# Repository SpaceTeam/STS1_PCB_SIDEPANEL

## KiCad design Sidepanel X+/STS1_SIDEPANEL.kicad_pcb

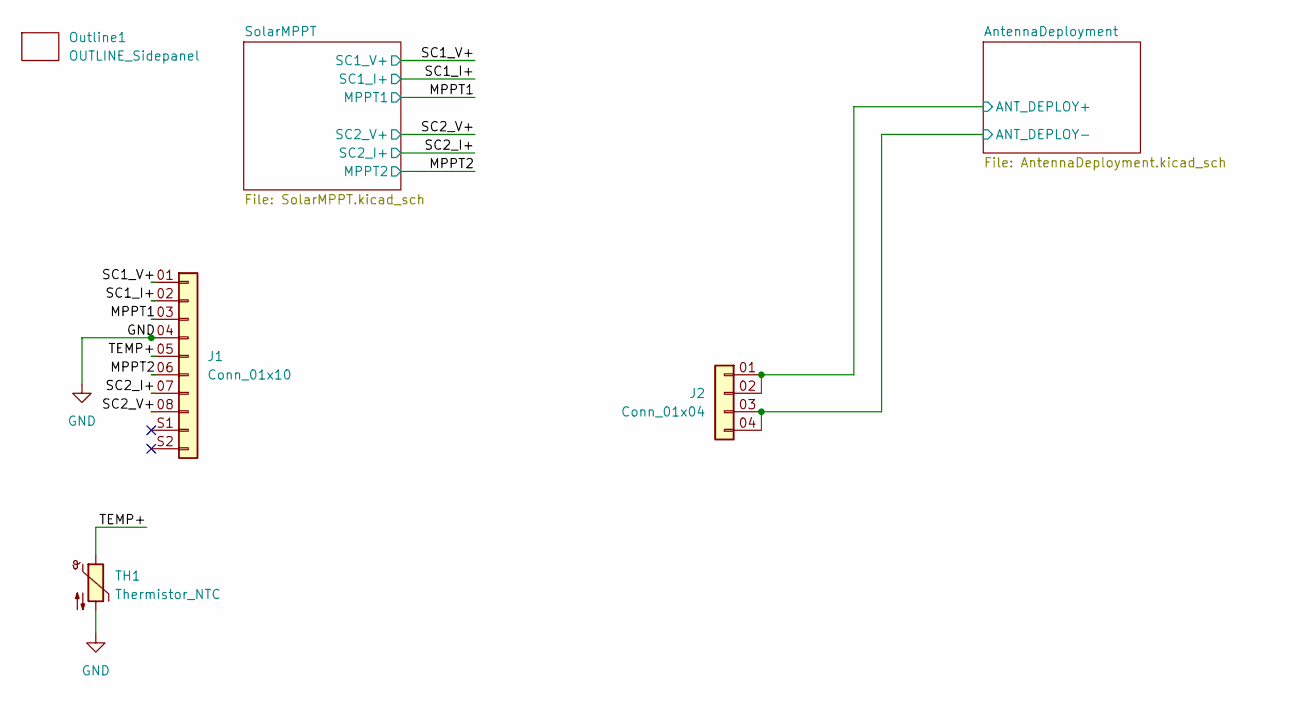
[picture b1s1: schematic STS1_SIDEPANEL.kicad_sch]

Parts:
J1: Conn_01x10; SAMTEC_T1M-08-F-SH-L
J2: Conn_01x04; SAMTEC_T1M-04-X-SV-L
Outline1: OUTLINE_Sidepanel; OUTLINE_SidepanelX+
TH1: Thermistor_NTC; R_0805_2012Metric_Pad1.20x1.40mm_HandSolder

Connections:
/AntennaDeployment/ANT_DEPLOY+: J2.01 (Pin_1), J2.02 (Pin_2); also elsewhere on the board
/AntennaDeployment/ANT_DEPLOY-: J2.03 (Pin_3), J2.04 (Pin_4); also elsewhere on the board
/MPPT1: J1.03 (Pin_3); also elsewhere on the board
/MPPT2: J1.06 (Pin_6); also elsewhere on the board
/SC1_I+: J1.02 (Pin_2); also elsewhere on the board
/SC1_V+: J1.01 (Pin_1); also elsewhere on the board
/SC2_I+: J1.07 (Pin_7); also elsewhere on the board
/SC2_V+: J1.08 (Pin_8); also elsewhere on the board
/TEMP+: J1.05 (Pin_5), TH1.1
GND: J1.04 (Pin_4), TH1.2; also elsewhere on the board

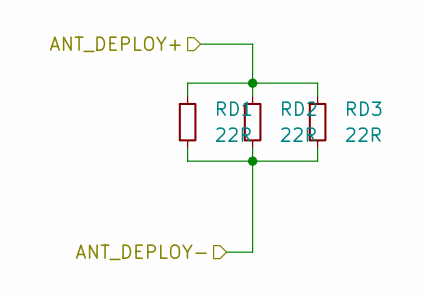
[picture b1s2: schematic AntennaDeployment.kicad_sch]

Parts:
RD1, RD2, RD3: 22R; R_MiniMELF_MMA-0204

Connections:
/AntennaDeployment/ANT_DEPLOY+: RD1.1, RD2.1, RD3.1; also elsewhere on the board
/AntennaDeployment/ANT_DEPLOY-: RD1.2, RD2.2, RD3.2; also elsewhere on the board

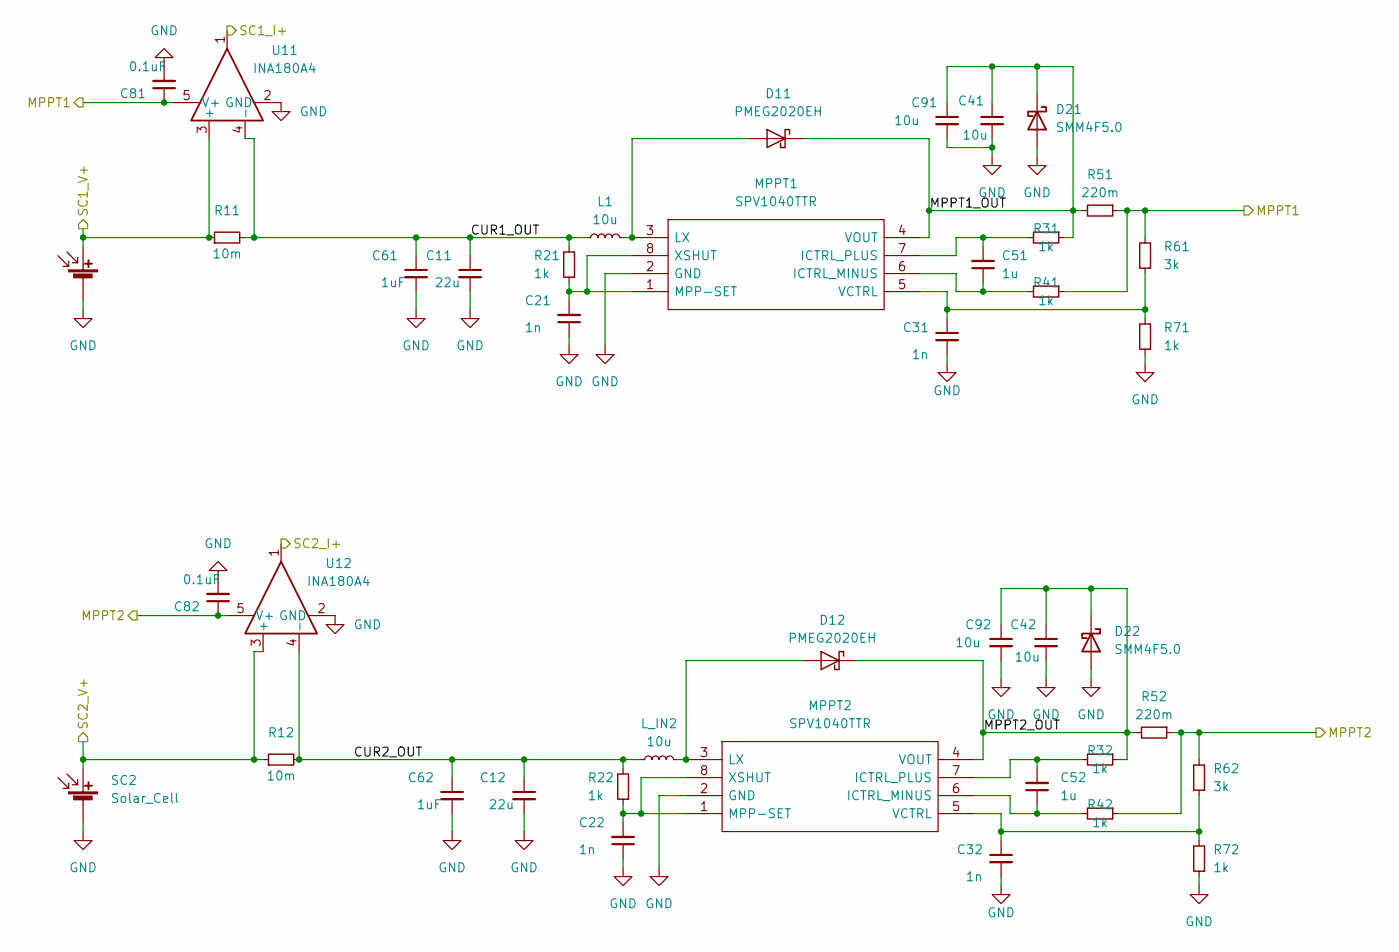
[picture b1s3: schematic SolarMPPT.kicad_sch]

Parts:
C11, C12: 22u; C_0805_2012Metric
C21, C22, C31, C32: 1n; C_0603_1608Metric
C41, C42, C91, C92: 10u; C_0805_2012Metric
C51, C52: 1u; C_0603_1608Metric
C61, C62: 1uF; C_0805_2012Metric
C81, C82: 0.1uF; C_0603_1608Metric
D11, D12: PMEG2020EH; D_SOD-123F
D21, D22: SMM4F5.0; DIO_SMM4F5.0A-TR
L1: 10u; IND_XAL6060-103MEC
L_IN2: 10u; IND_XAL6060-103MEC
MPPT1, MPPT2: SPV1040TTR; TSSOP-8_4.4x3mm_P0.65mm; Mouser Part Number 511-SPV1040TTR
R11, R12: 10m; R_0805_2012Metric
R21, R22, R31, R32, R41, R42, R71, R72: 1k; R_0603_1608Metric
R51, R52: 220m; R_0805_2012Metric
R61, R62: 3k; R_0603_1608Metric
SC1: Solar_Cell; 3G30A_40x80_Z_SC1
SC2: Solar_Cell; 3G30A_40x80_Z_SC2
U11, U12: INA180A4; SOT-23-5

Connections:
/MPPT1: C81.1, R41.1, R51.1, R61.2, U11.5 (V+); also elsewhere on the board
/MPPT2: C82.1, R42.1, R52.1, R62.2, U12.5 (V+); also elsewhere on the board
/SC1_I+: U11.1; also elsewhere on the board
/SC1_V+: R11.1, SC1.1 (+), U11.3 (+); also elsewhere on the board
/SC2_I+: U12.1; also elsewhere on the board
/SC2_V+: R12.1, SC2.1 (+), U12.3 (+); also elsewhere on the board
/SolarMPPT/CUR1_OUT: C11.1, C61.1, L1.1, R11.2, R21.2, U11.4 (-)
/SolarMPPT/CUR2_OUT: C12.1, C62.1, L_IN2.1, R12.2, R22.2, U12.4 (-)
/SolarMPPT/MPPT1_OUT: C41.1, C91.1, D11.1 (K), D21.1 (K), MPPT1.4 (VOUT), R31.1, R51.2
/SolarMPPT/MPPT2_OUT: C42.1, C92.1, D12.1 (K), D22.1 (K), MPPT2.4 (VOUT), R32.1, R52.2
GND: C11.2, C12.2, C21.1, C22.1, C31.2, C32.2, C41.2, C42.2, C61.2, C62.2, C81.2, C82.2, C91.2, C92.2, D21.2 (A), D22.2 (A), MPPT1.2 (GND), MPPT2.2 (GND), R71.1, R72.1, SC1.2 (-), SC2.2 (-), U11.2 (GND), U12.2 (GND); also elsewhere on the board
unnamed: D11.2 (A), L1.2, MPPT1.3 (LX)
unnamed: D12.2 (A), L_IN2.2, MPPT2.3 (LX)
unnamed: C51.1, MPPT1.6 (ICTRL_MINUS), R41.2
unnamed: C51.2, MPPT1.7 (ICTRL_PLUS), R31.2
unnamed: C21.2, MPPT1.1 (MPP-SET), MPPT1.8 (XSHUT), R21.1
unnamed: C31.1, MPPT1.5 (VCTRL), R61.1, R71.2
unnamed: C52.1, MPPT2.6 (ICTRL_MINUS), R42.2
unnamed: C52.2, MPPT2.7 (ICTRL_PLUS), R32.2
unnamed: C22.2, MPPT2.1 (MPP-SET), MPPT2.8 (XSHUT), R22.1
unnamed: C32.1, MPPT2.5 (VCTRL), R62.1, R72.2

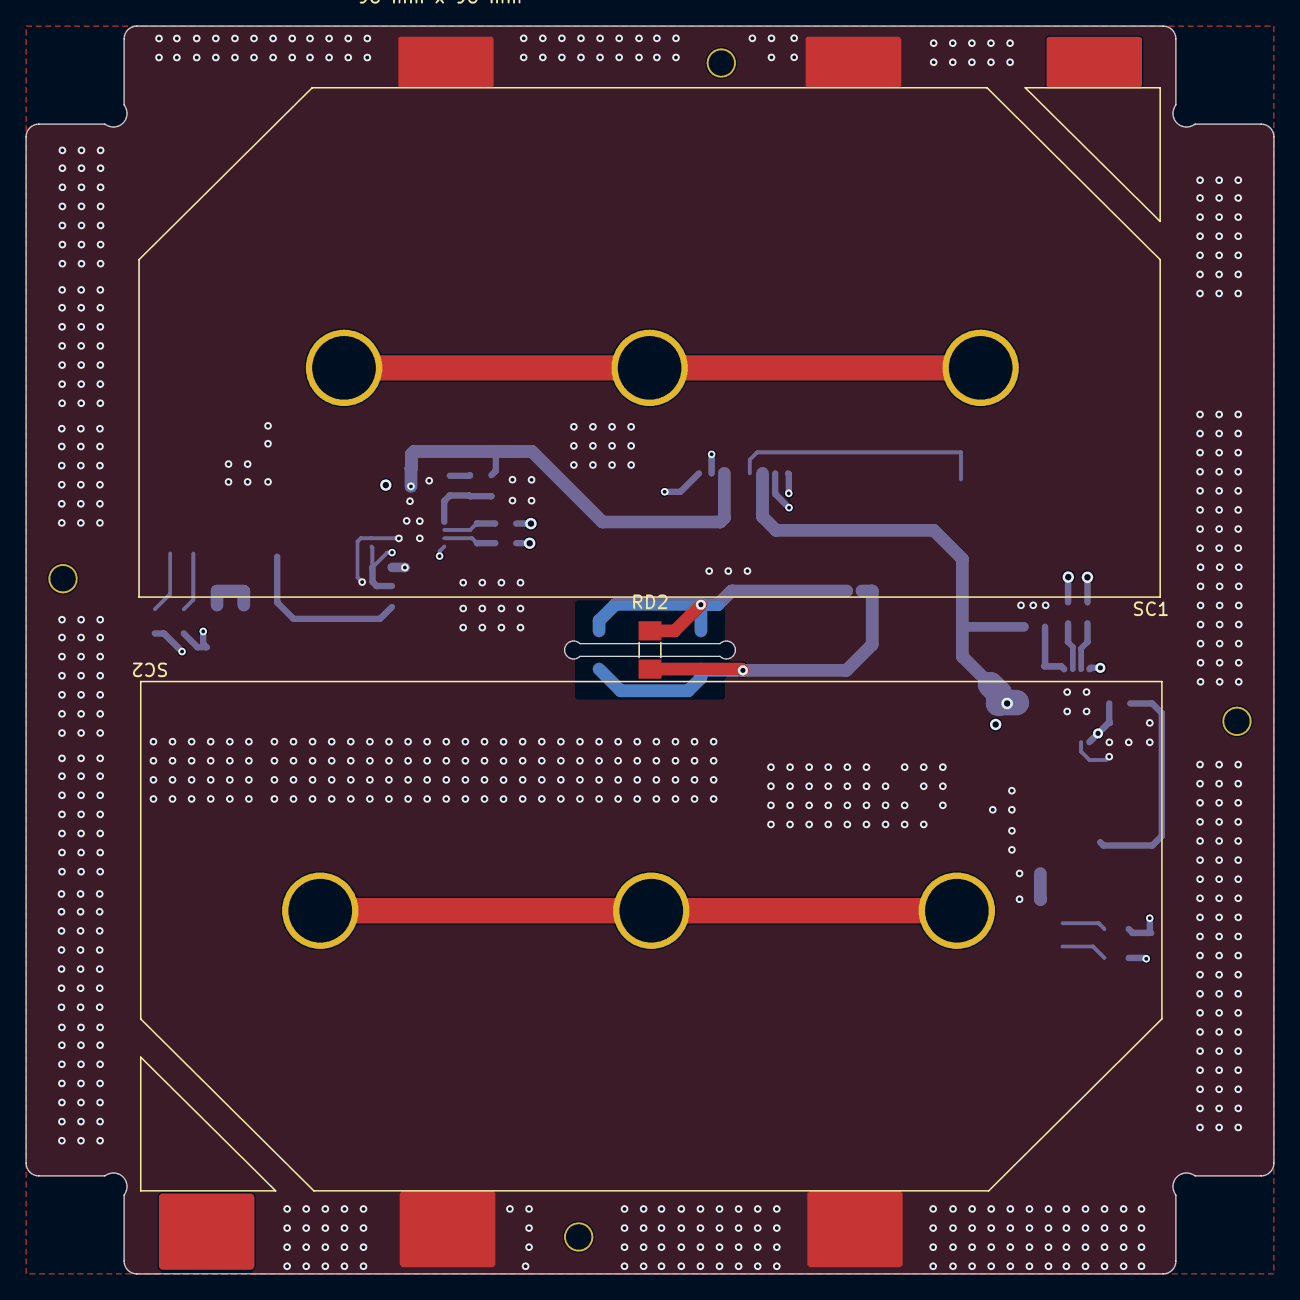
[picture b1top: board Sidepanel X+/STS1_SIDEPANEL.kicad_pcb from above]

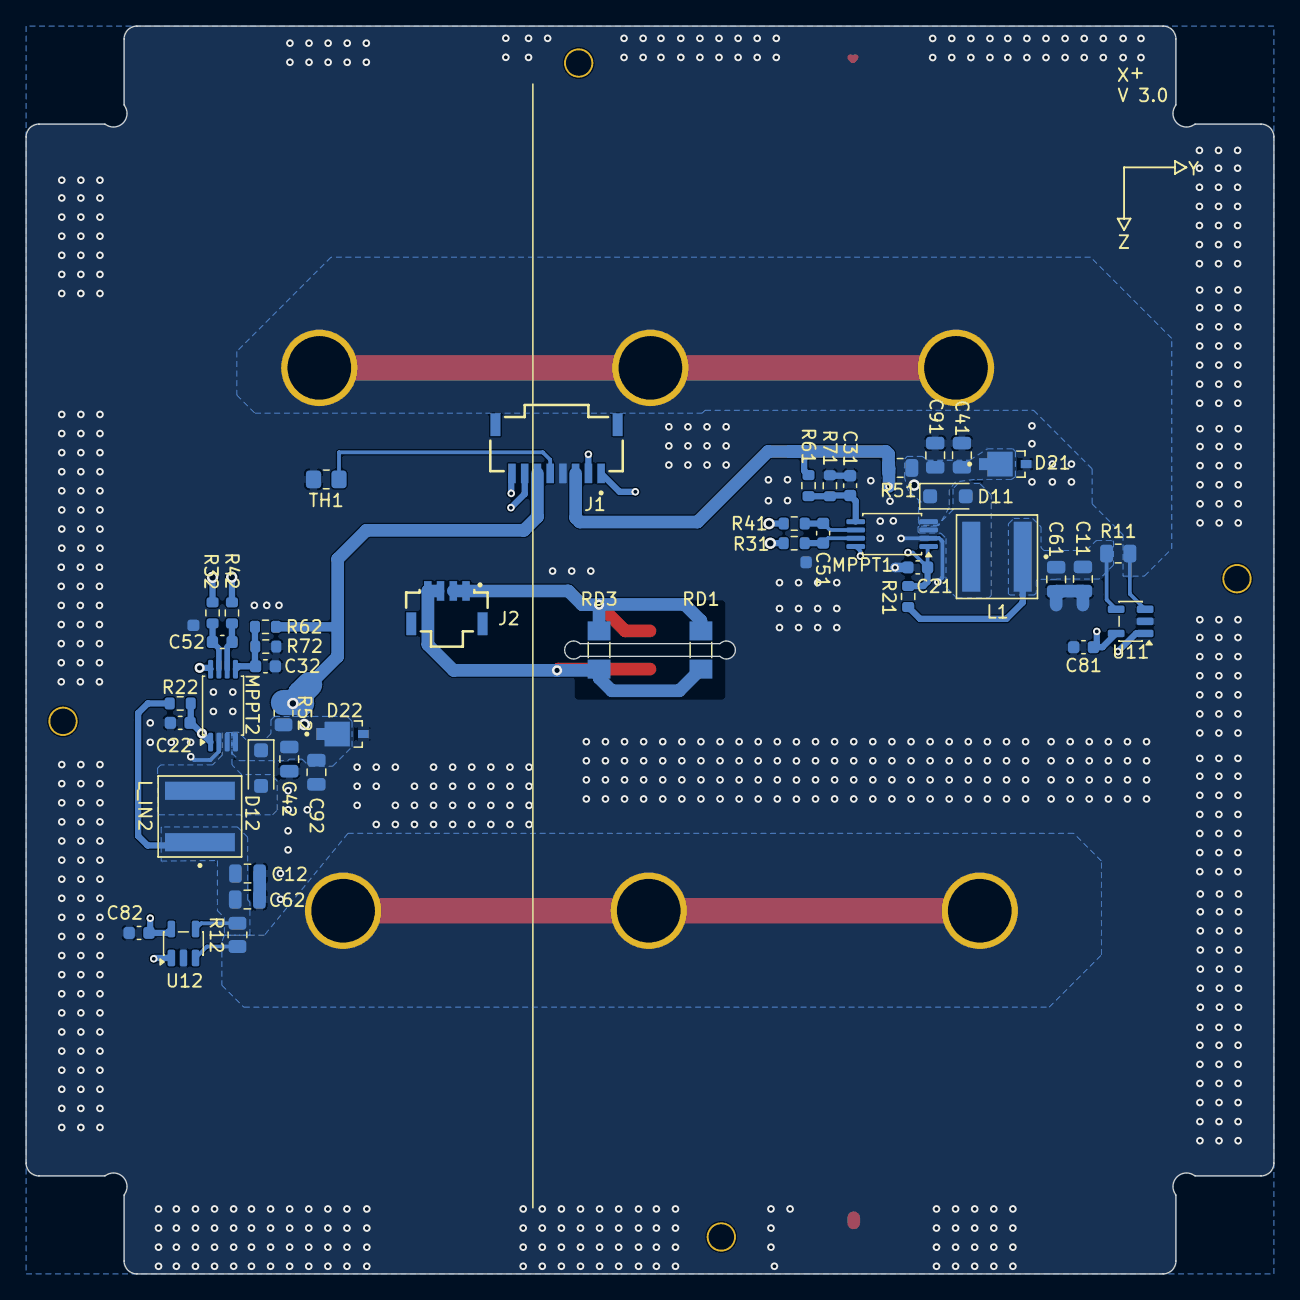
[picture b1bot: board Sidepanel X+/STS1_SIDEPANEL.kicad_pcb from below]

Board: 4 copper layers, 98.0 x 98.0 mm, 49 parts (45 on the bottom side), 24 nets.

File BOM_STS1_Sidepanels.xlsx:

ID | Bezeichner | Footprint | Count | Bezeichnung |  | Note
1 | RD2,RD1,RD3 | R_MiniMELF_MMA-0204 | 3 | 22R
2 | C41,C42 | C_0805_2012Metric | 2 | 22u 10V |  |  | MOUSER_Invoice_33231465.pdf
3 | C11,C12,C61,C62 | C_0805_2012Metric | 4 | 22u 6.3V |  |  | MOUSER_Invoice_33231465.pdf
4 | TH1 | R_0805_2012Metric_Pad1.20x1.40mm_HandSolder | 1 | Thermistor_NTC |  |  | MOUSER_Invoice_33231465.pdf
5 | J3 | M808280442 | 1 | Conn_02x02_Odd_Even |  | Space Team assembles it
6 | D21,D22 | DIO_SMM4F5.0A-TR | 2 | SMM4F5.0 |  |  | MOUSER_Invoice_33231465.pdf
7 | MPPT1,MPPT2 | TSSOP-8_4.4x3mm_P0.65mm | 2 | SPV1040TTR |  |  | SPV1040_Invoice
8 | R21,R22,R31,R32,R41,R42,R71,R72 | R_0603_1608Metric | 8 | 1k |  |  | MOUSER_Invoice_33231465.pdf
9 | D11,D12 | D_SOD-123F | 2 | PMEG2020EH |  |  | MOUSER_Invoice_33231465.pdf
10 | R61,R62 | R_0603_1608Metric | 2 | 3k |  |  | MOUSER_Invoice_33231465.pdf
11 | R11,R12 | R_0805_2012Metric | 2 | 10m |  |  | MOUSER_Invoice_33231465.pdf
12 | U11,U12 | SOT-23-5 | 2 | INA180A4 |  |  | MOUSER_Invoice_33231465.pdf
13 | R51,R52 | R_0805_2012Metric | 2 | 220m |  |  | MOUSER_Invoice_33231465.pdf
14 | C21,C22,C31,C32 | C_0603_1608Metric | 4 | 1n |  |  | MOUSER_Invoice_33231465.pdf
15 | C51,C52 | C_0603_1608Metric | 2 | 1u |  |  | MOUSER_Invoice_33231465.pdf
16 | J1 | SAMTEC_ZF5S-08-01-T-WT | 1 | Conn_01x10 |  |  | MOUSER_Invoice_33231465.pdf
17 | L_IN2,L1 | IND_XAL6060-103MEC | 2 | 10u |  |  | DK_INVOICE_106491210.pdf

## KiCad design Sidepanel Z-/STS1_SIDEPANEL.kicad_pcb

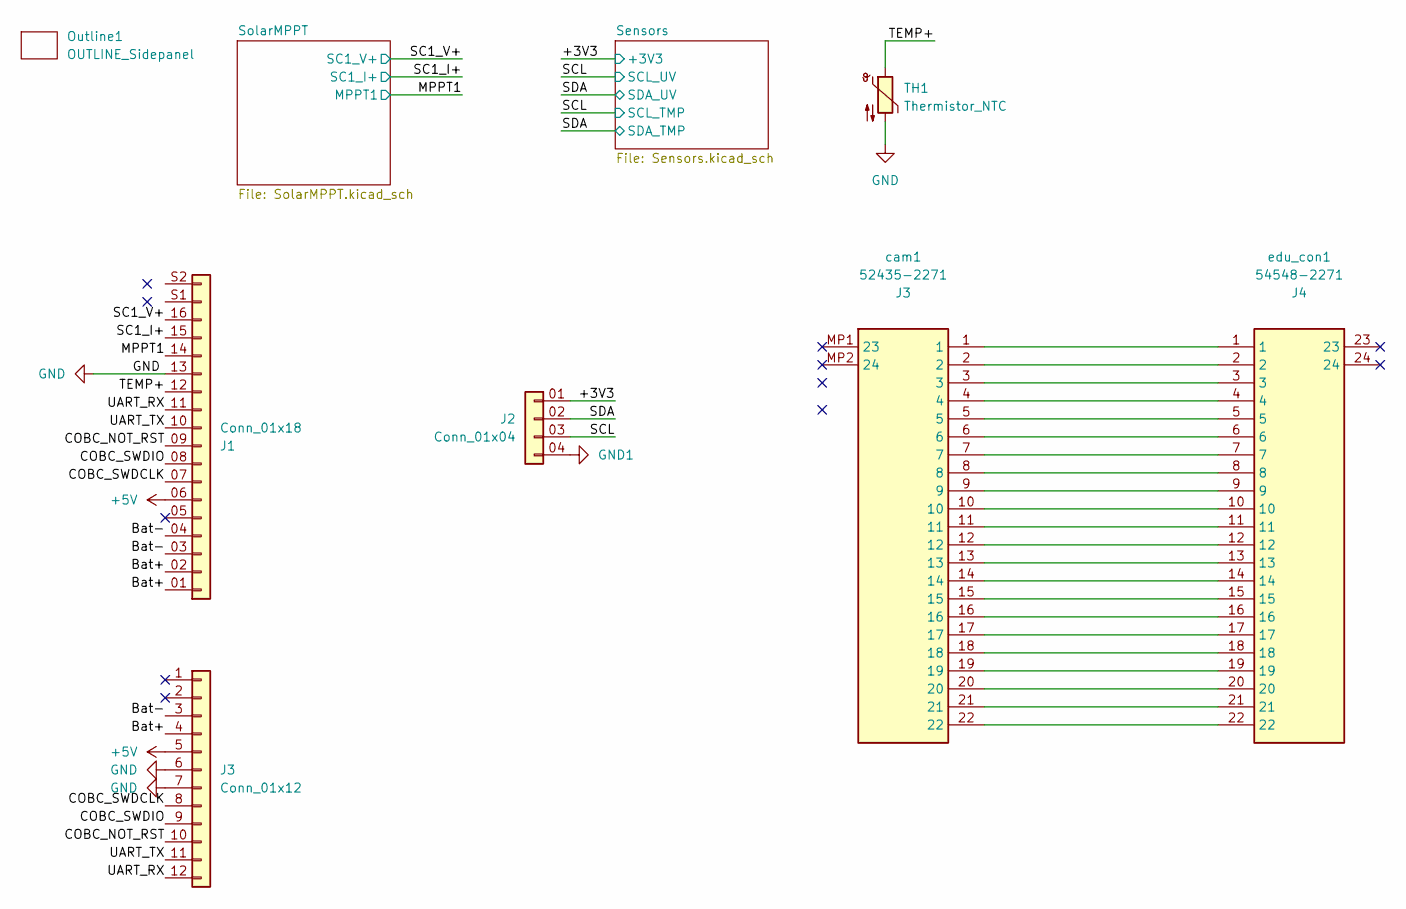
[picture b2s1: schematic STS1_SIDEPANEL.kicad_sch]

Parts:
J1: Conn_01x18; SAMTEC_T1M-16-F-SH-L
J2: Conn_01x04; SAMTEC_T1M-04-X-SH-L
J3: Conn_01x12; conn_to_panel
Outline1: OUTLINE_Sidepanel; OUTLINE_SidepanelZ-
TH1: Thermistor_NTC; R_0805_2012Metric_Pad1.20x1.40mm_HandSolder
cam1: 52435-2271; 524352271; Manufacturer_Part_Number 54548-2271; Mouser Part Number 538-54548-2271
edu_con1: 54548-2271; 545482271; Manufacturer_Part_Number 54548-2271; Mouser Part Number 538-54548-2271

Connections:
+5V: J1.06 (Pin_6), J3.5
/+3V3: J2.01 (Pin_1); also elsewhere on the board
/Bat+: J1.01 (Pin_1), J1.02 (Pin_2), J3.4
/Bat-: J1.03 (Pin_3), J1.04 (Pin_4), J3.3
/COBC_NOT_RST: J1.09 (Pin_9), J3.10
/COBC_SWDCLK: J1.07 (Pin_7), J3.8
/COBC_SWDIO: J1.08 (Pin_8), J3.9
/MPPT1: J1.14; also elsewhere on the board
/SC1_I+: J1.15; also elsewhere on the board
/SC1_V+: J1.16; also elsewhere on the board
/SCL: J2.03 (Pin_3); also elsewhere on the board
/SDA: J2.02 (Pin_2); also elsewhere on the board
/TEMP+: J1.12, TH1.1
/UART_RX: J1.11, J3.12
/UART_TX: J1.10, J3.11
GND: J1.13, J3.6, J3.7, TH1.2; also elsewhere on the board
GND1: J2.04 (Pin_4); also elsewhere on the board
unnamed: cam1.1, edu_con1.1
unnamed: cam1.2, edu_con1.2
unnamed: cam1.3, edu_con1.3
unnamed: cam1.4, edu_con1.4
unnamed: cam1.5, edu_con1.5
unnamed: cam1.6, edu_con1.6
unnamed: cam1.7, edu_con1.7
unnamed: cam1.8, edu_con1.8
unnamed: cam1.9, edu_con1.9
unnamed: cam1.10, edu_con1.10
unnamed: cam1.11, edu_con1.11
unnamed: cam1.12, edu_con1.12
unnamed: cam1.13, edu_con1.13
unnamed: cam1.14, edu_con1.14
unnamed: cam1.15, edu_con1.15
unnamed: cam1.16, edu_con1.16
unnamed: cam1.17, edu_con1.17
unnamed: cam1.18, edu_con1.18
unnamed: cam1.19, edu_con1.19
unnamed: cam1.20, edu_con1.20
unnamed: cam1.21, edu_con1.21
unnamed: cam1.22, edu_con1.22

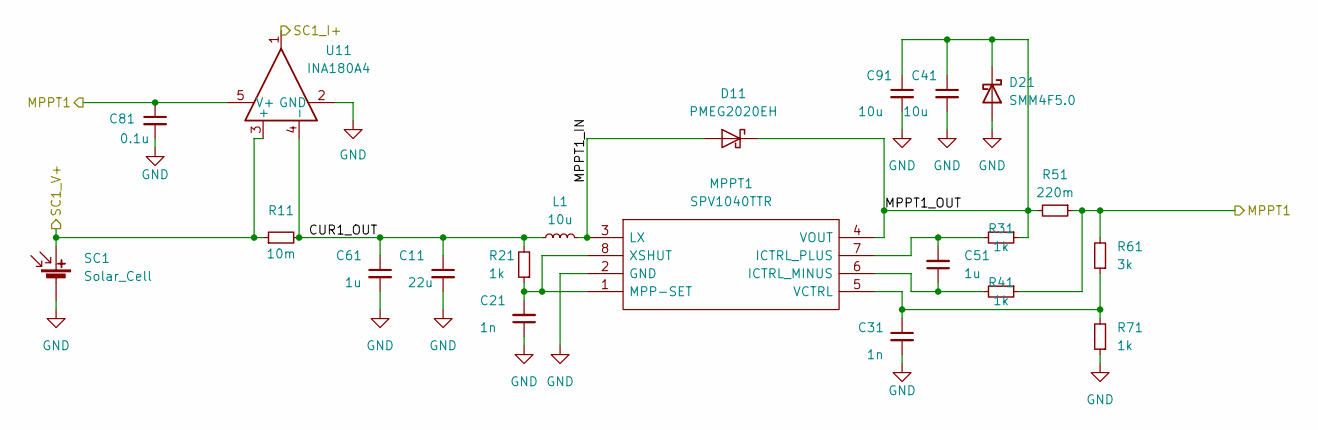
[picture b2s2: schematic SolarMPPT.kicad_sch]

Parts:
C11: 22u; C_0805_2012Metric
C21, C31: 1n; C_0603_1608Metric
C41, C91: 10u; C_0805_2012Metric
C51: 1u; C_0603_1608Metric
C61: 1u; C_0805_2012Metric
C81: 0.1u; C_0603_1608Metric
D11: PMEG2020EH; D_SOD-123F
D21: SMM4F5.0; DIO_SMM4F5.0A-TR
L1: 10u; IND_XAL6060-103MEC
MPPT1: SPV1040TTR; TSSOP-8_4.4x3mm_P0.65mm; Mouser Part Number 511-SPV1040TTR
R11: 10m; R_0805_2012Metric
R21, R31, R41, R71: 1k; R_0603_1608Metric
R51: 220m; R_0805_2012Metric
R61: 3k; R_0603_1608Metric
SC1: Solar_Cell; 3G30A_40x80
U11: INA180A4; SOT-23-5

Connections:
/MPPT1: C81.1, R41.1, R51.1, R61.2, U11.5 (V+); also elsewhere on the board
/SC1_I+: U11.1; also elsewhere on the board
/SC1_V+: R11.1, SC1.1 (+), U11.3 (+); also elsewhere on the board
/SolarMPPT/CUR1_OUT: C11.1, C61.1, L1.1, R11.2, R21.2, U11.4 (-)
/SolarMPPT/MPPT1_IN: D11.2 (A), L1.2, MPPT1.3 (LX)
/SolarMPPT/MPPT1_OUT: C41.1, C91.1, D11.1 (K), D21.1, MPPT1.4 (VOUT), R31.1, R51.2
GND: C11.2, C21.1, C31.2, C41.2, C61.2, C81.2, C91.2, D21.2, MPPT1.2 (GND), R71.1, SC1.2 (-), U11.2 (GND); also elsewhere on the board
unnamed: C51.1, MPPT1.6 (ICTRL_MINUS), R41.2
unnamed: C51.2, MPPT1.7 (ICTRL_PLUS), R31.2
unnamed: C21.2, MPPT1.1 (MPP-SET), MPPT1.8 (XSHUT), R21.1
unnamed: C31.1, MPPT1.5 (VCTRL), R61.1, R71.2

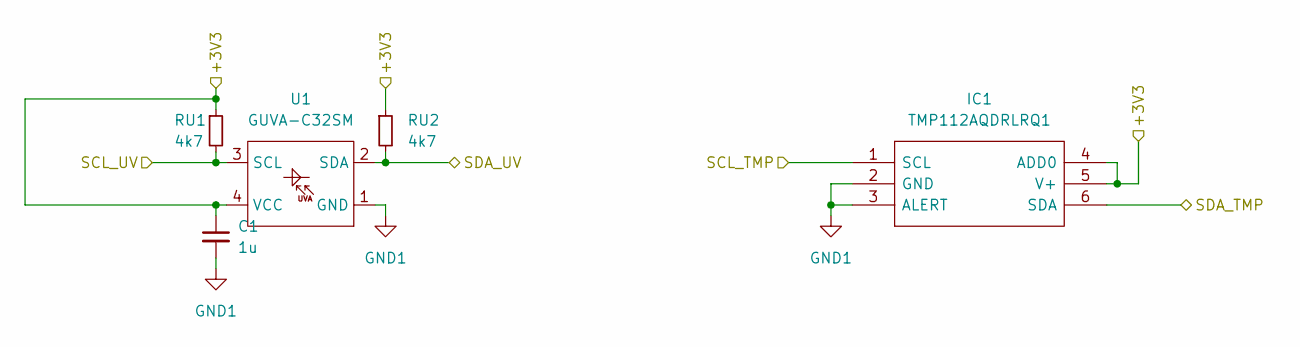
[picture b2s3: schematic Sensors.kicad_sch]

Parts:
C1: 1u; C_0603_1608Metric
IC1: TMP112AQDRLRQ1; SOT-563; Mouser Part Number 595-TMP112AQDRLRQ1
RU1, RU2: 4k7; R_0603_1608Metric
U1: GUVA-C32SM; OLGA

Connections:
/+3V3: C1.1, IC1.4 (ADD0), IC1.5 (V+), RU1.1, RU2.1, U1.4 (VCC); also elsewhere on the board
/SCL: IC1.1 (SCL), RU1.2, U1.3 (SCL); also elsewhere on the board
/SDA: IC1.6 (SDA), RU2.2, U1.2 (SDA); also elsewhere on the board
GND1: C1.2, IC1.2 (GND), IC1.3 (ALERT), U1.1 (GND); also elsewhere on the board

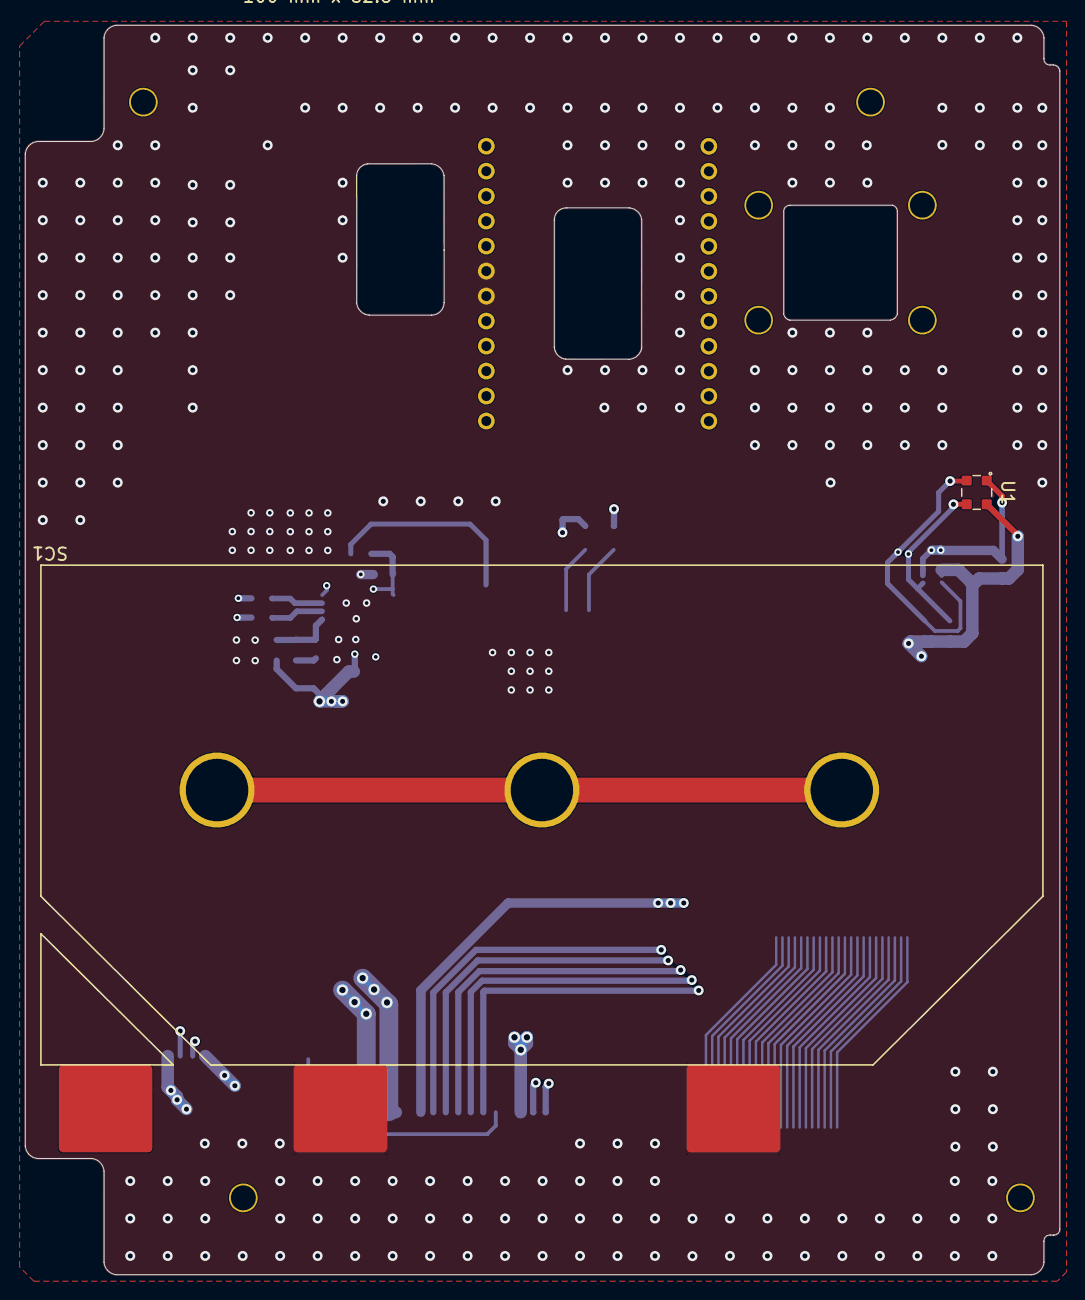
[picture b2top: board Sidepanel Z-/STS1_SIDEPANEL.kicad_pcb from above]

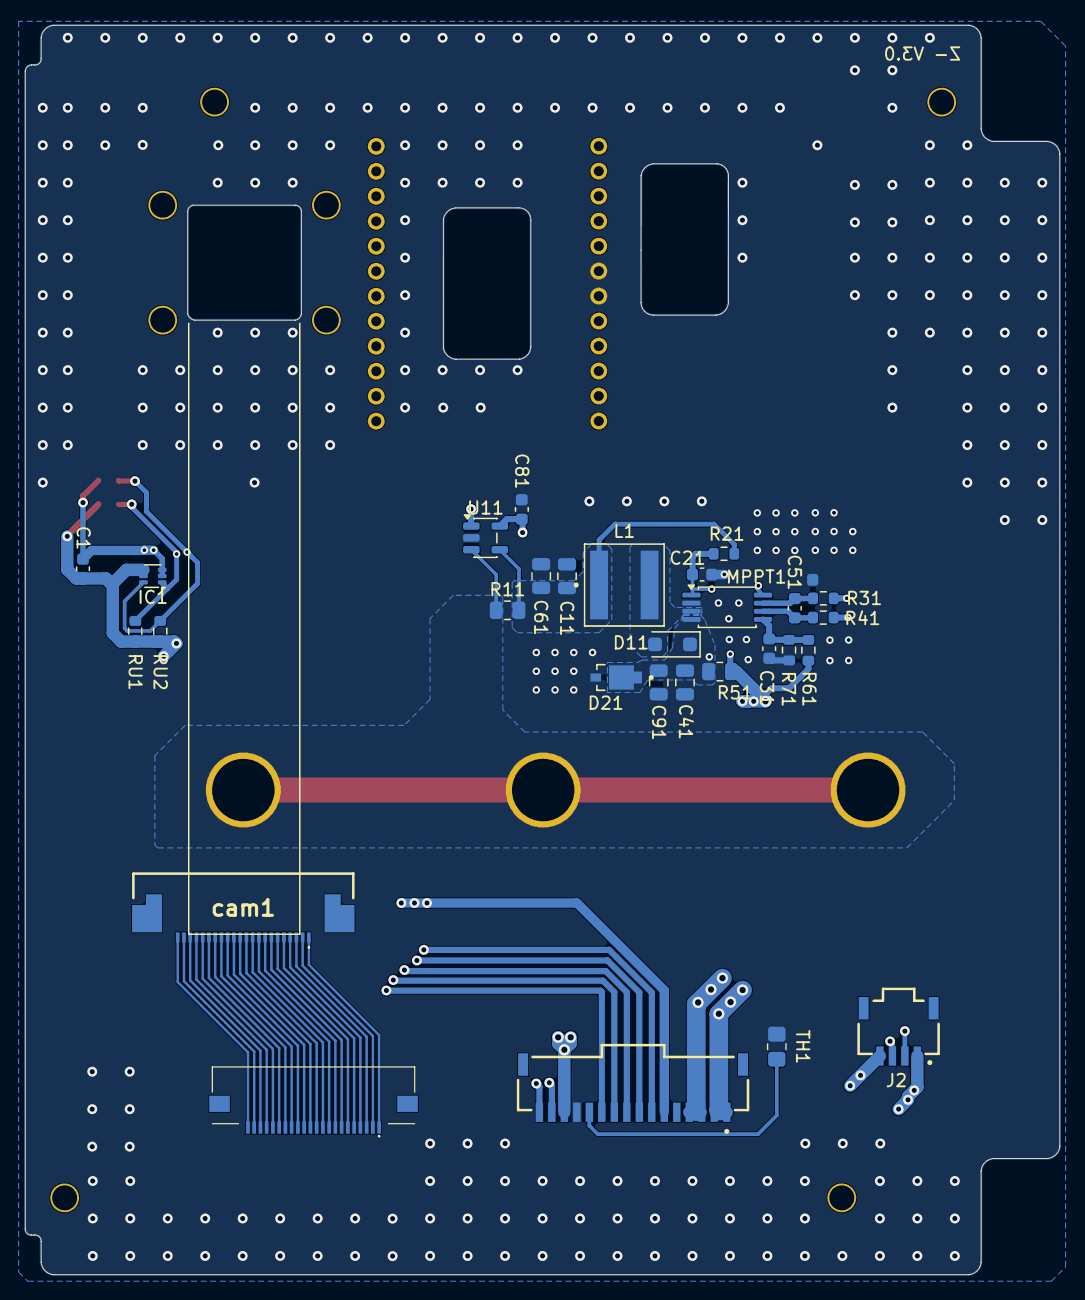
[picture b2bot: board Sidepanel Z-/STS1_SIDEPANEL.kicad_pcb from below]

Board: 4 copper layers, 82.8 x 100.0 mm, 34 parts (29 on the bottom side), 46 nets.

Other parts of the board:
uci_conn: conn_to_panel

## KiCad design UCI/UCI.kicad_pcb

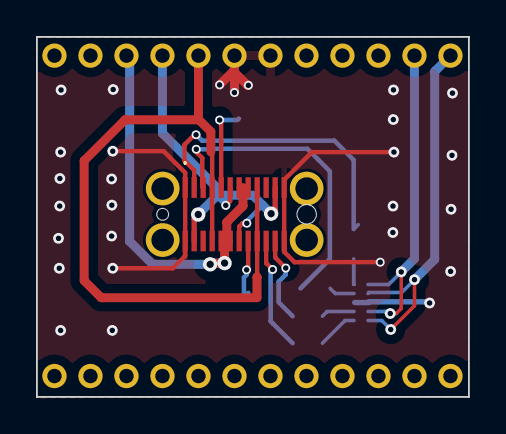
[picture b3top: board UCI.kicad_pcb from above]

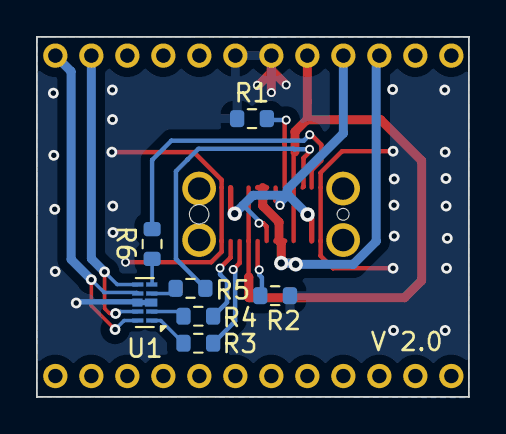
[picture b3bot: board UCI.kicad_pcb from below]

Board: 2 copper layers, 24.0 x 20.0 mm, 8 parts (7 on the bottom side), 16 nets.

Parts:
J1: USB_C_Receptacle; USB4160030170C
R1, R2: 5.11k; R_0603_1608Metric
R3, R4, R5, R6: 1k; R_0603_1608Metric
U1: ESD224DQA; Diodes_UDFN-10_1.0x2.5mm_P0.5mm

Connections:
1: J1.A2 (TX1+), R6.1
2: J1.A3 (TX1-), R5.1
3: J1.B3 (TX2-), R3.1
4: J1.B2 (TX2+), R4.1
+5V: J1.A4 (VBUS), J1.A9 (VBUS), J1.B4 (VBUS), J1.B9 (VBUS)
Bat+: J1.A6 (D+), J1.A11 (RX2+), J1.B6 (D+), J1.B11 (RX1+)
Bat-: J1.A7 (D-), J1.A8 (SBU1), J1.B7 (D-), J1.B8 (SBU2)
GND: J1.A1 (GND), J1.A12 (GND), J1.B1 (GND), J1.B12 (GND), R1.1, R2.1, U1.3 (VSS), U1.8 (VSS)
unnamed: J1.A5 (CC1), R1.2
unnamed: J1.B5 (CC2), R2.2
unnamed: R3.2, U1.1
unnamed: R4.2, U1.2
unnamed: R5.2, U1.4
unnamed: R6.2, U1.5
UCI_COBC_UART_RX: U1.7, U1.10
UCI_COBC_UART_TX: U1.6, U1.9

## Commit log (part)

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2022-07-06 Side Panels
2022-07-31 Review Ready for V2.0
2022-08-01 Paar Fehler behoben, Z+ no MOSFET
2022-08-02 Further fixes, still some open
2022-08-05 Next fix
2022-08-09 release_2.0, Ordered PCBs
2023-04-11 Diode D1 angebracht
2023-04-29 Renamed the Sidepanel folders (X- to Y-, X+ to Y+, Y to X)
2023-07-08 changed the outline of the pcbs + new axis orientaion + changed the footprint of the solar cells
2023-07-27 Fixed some DRC errors.
2023-09-09 Adjusted the panel naming so that it conforms to the coordinate system convention governed by the Cubesat Design Specification.
2023-09-24 Added step files of the panels
2023-09-27 adjusted the cutout for the camera
2023-10-03 changes to the solar cells footprint, added camera mounts
2023-10-04 small changes of the connectors position
2023-10-04 small changes to the connectors position
2023-10-06 small adjustments
2023-10-07 updated the step files
2023-10-09 changes to the solar cell footprint + added alternative current sensing solution
2023-10-09 update step files
2023-10-12 changed the x+ and x- axis
2023-10-14 added the libraries for the specific components
2023-10-14 added the libraries
2023-10-14 update to step file
2023-10-15 changes to the position of the connectors and some components
2023-10-15 selected the Y+ panel for Y
2023-10-16 Adjusted EPS connector on the Z panel, so that it does not stretch over the heater resistors of the antenna release mechanism.
2023-10-16 Adjusted the position of the connector on the X+ and X- panel, so that there is more space to the connectors on the EPS.
2023-10-16 changes in gerber settings
2023-10-17 Renamed Sidepanel Z+ to Sidepanel Z- and removed Step files.
2023-10-26 removed the solder mask for the solar cells, added the dimensions of panels on silkscreen
2023-10-26 changed the naming on the silkscreen from z+ to z-
2023-10-27 removed the solder paste for the solar cells
2023-10-27 moved the dimensions of the panels in the user.1 layer
2023-10-27 moved the dimensions back to silkscreen
2023-10-27 moved the dimension back to the silkscreen
2023-11-02 added the F.Mask for the through holes of the solar cells
2023-11-11 Create LICENSE
2023-12-29 the first version of the flex pcb
2023-12-29 added the flex pcb
2024-01-31 added the flex PCBs for the camera, X+, Z+ and Y+ and rounded some corners of the X+ cutout
2024-02-10 fix for the issues: #19, #18 moved some components from the edge away to avoid collisions with the new structure
2024-04-07 added the UCI
2024-04-15 Added small modifications to the existing flex PCBs plus the new ones: Y- and X-.
2024-06-04 Changed the layout of all the sidepanel PCBs to mitigate the problems that arised from the bad previous design.
2024-06-09 Added a separate ground for the EDU sensors and did some small changes for ordering.
2024-06-09 Commit before the order.
2024-06-12 small changes before the order
2024-06-19 Replaced buried vias with through vias and modified footprint of solar cell, so it is not shorted.
2024-08-04 Restructure FlexPCB folders, SP_EPS_YP done
2024-08-04 Add SP EPS ZP
2024-08-04 Add SP EPS ZM
2024-08-04 ADD SP EPS YM and XP
2024-08-09 moved the connectors, changed the footprint of the input and output capacitors and splitted the input capacitor in two
2024-08-11 small change in the routing
2024-08-15 Update the EPS FlexPCBs, with correct top/down and crossed out
2024-08-17 Z+ Cam Connector Rerout & 90deg trace removal
2024-08-17 Z- Cam Connerctor Rerout, add vias & 90deg trace removal
2024-08-19 Minor improvements. - Added some vias to current carrying traces. - Added edge outline to sidepanel z+ again. - Fixed some minor warnings.
2024-08-20 Add FM Gerber Production files
2024-08-20 Restructure Deliveryfiles
2024-08-20 Added position files.
2024-08-21 Current BOM status
2024-08-22 Changed the values of the VCTRL resistors.
2024-08-22 Update Dhruva FM order
2024-08-22 Refactor Zipnames
2024-08-23 Sent Dhruva the BOM_STS1_Sidepanels
2024-08-28 Zwischenspeicherung Customs
2024-09-02 Updated according to the review from Dhruva.
2024-09-02 Refilled all zones of the PCB.
2024-09-02 Update BOM status and add an invoice
2024-09-02 Update to V1.2, fix Mounting holes
2024-09-03 Move final Export docuemnts to the Nextcloud
2024-09-07 Update SP_EDU_Cam_ZM_Flex for FM
2024-09-07 Update SP_EDU_Z_Flex for FM
2024-09-07 Update SP_EDU_Flex_TopDown for FM
2024-09-08 Update SP_EDU_YP_Flex for FM
2024-09-08 Update SP_EDU_YM_Flex for FM
2024-09-08 Store Order Files FM FlexPCBs V1.0
2024-10-12 changed all vias from blind to trough and removed the unused pins of the uci connector
2024-10-12 removed the unused pins also from the PCB
2024-10-12 chaned the connectors for the cameras from buttom to top contact
2024-10-13 connected the vias for the solar cell together
2024-10-15 moved the camera connectors to be sure that the cable can be inserted
2024-10-15 Removed some unnecessary drawings from the silkscreen.
2024-10-15 Generated the gerber files and moved some vias around.
2024-10-27 Changed one of the inputs capacitors for all panels with one of 1 uF and lower ESR and moved some traces that were under the inductor.
2024-11-09 generated the gerber files for ordering
2024-11-09 Add V1.4 which will be ordered
2025-01-20 update of the files for JLC order
